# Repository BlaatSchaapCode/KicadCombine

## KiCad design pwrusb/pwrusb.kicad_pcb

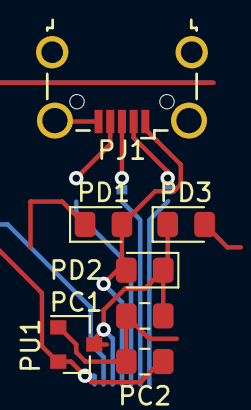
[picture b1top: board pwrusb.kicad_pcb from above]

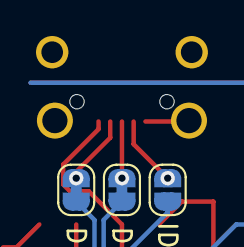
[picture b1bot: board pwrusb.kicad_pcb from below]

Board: 2 copper layers, 10 parts (3 on the bottom side), 7 nets.

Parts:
PC1, PC2: 1uF; C_0805_2012Metric_Pad1.15x1.40mm_HandSolder
PD1, PD2, PD3: D; D_0805_2012Metric_Pad1.15x1.40mm_HandSolder
PJ1: USB_B_Mini; USB_Micro-B_Wuerth_629105150521_CircularHoles
PSJ1: D+; SolderJumper-2_P1.3mm_Bridged_RoundedPad1.0x1.5mm
PSJ2: D-; SolderJumper-2_P1.3mm_Bridged_RoundedPad1.0x1.5mm
PSJ3: ID; SolderJumper-2_P1.3mm_Open_RoundedPad1.0x1.5mm
PU1: MCP1700-3302E_SOT23; SOT-23

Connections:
GND: PC1.2, PC2.2, PJ1.5, PJ1.6, PU1.1
unnamed: PJ1.2, PSJ2.1
unnamed: PJ1.3, PSJ1.1
unnamed: PJ1.4, PSJ3.1
VBUS: PD1.2, PD2.2, PJ1.1
VDD: PC2.1, PU1.2
VREG_IN: PC1.1, PD2.1, PD3.1, PU1.3

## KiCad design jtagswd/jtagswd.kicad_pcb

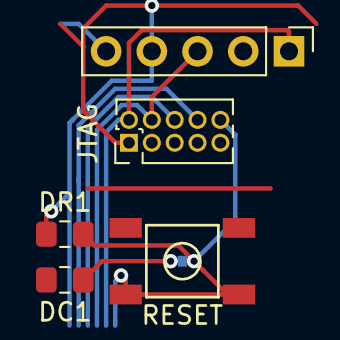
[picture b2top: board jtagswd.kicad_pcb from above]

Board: 2 copper layers, 6 parts (1 on the bottom side), 6 nets.

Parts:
DC1: 100nF; C_0805_2012Metric_Pad1.15x1.40mm_HandSolder
DJ1: JTAG; PinHeader_2x05_P1.27mm_Vertical
DJ2: Conn_01x05; PinHeader_1x05_P2.54mm_Vertical
DJP1: SolderJumper_2_Bridged; SolderJumper-2_P1.3mm_Bridged_RoundedPad1.0x1.5mm
DR1: 10K; R_0805_2012Metric_Pad1.15x1.40mm_HandSolder
DSW1: RESET; TS-1187

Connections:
GND: DC1.1, DJ1.3, DJ1.7, DJ1.9, DJ2.2, DSW1.2
unnamed: DC1.2, DJP1.2
TCK: DJ1.4, DJ2.3
TMS: DJ1.2, DJ2.1
VDD: DJ1.1, DJ2.4, DR1.1
~SRST: DJ1.10, DJP1.1, DR1.2, DSW1.1

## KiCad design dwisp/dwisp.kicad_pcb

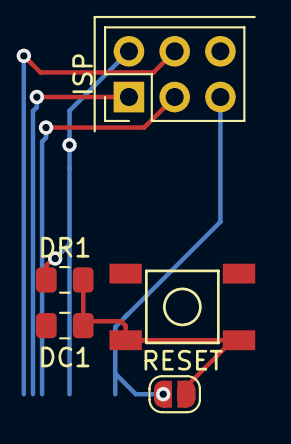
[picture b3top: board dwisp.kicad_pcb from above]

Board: 2 copper layers, 5 parts (0 on the bottom side), 4 nets.

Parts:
DC1: 100nF; C_0805_2012Metric_Pad1.15x1.40mm_HandSolder
DJ2: ISP; PinHeader_2x03_P2.54mm_Vertical
DJP1: SolderJumper_2_Open; SolderJumper-2_P1.3mm_Open_RoundedPad1.0x1.5mm
DR1: 10K; R_0805_2012Metric_Pad1.15x1.40mm_HandSolder
DSW1: RESET; TS-1187

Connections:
GND: DC1.1, DJ2.6, DSW1.2
unnamed: DC1.2, DJP1.2, DR1.2, DSW1.1
VDD: DJ2.2, DR1.1
~RESET: DJ2.5, DJP1.1

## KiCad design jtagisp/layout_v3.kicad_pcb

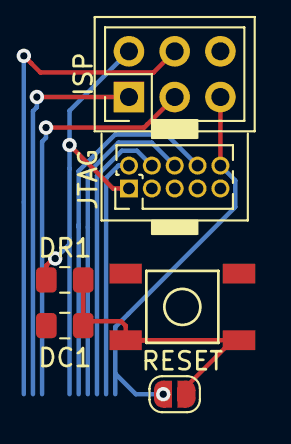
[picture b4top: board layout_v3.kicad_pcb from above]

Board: 2 copper layers, 6 parts (0 on the bottom side), 4 nets.

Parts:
DC1: 100nF; C_0805_2012Metric_Pad1.15x1.40mm_HandSolder
DJ1: JTAG; PinHeader_2x05_P1.27mm_Vertical
DJ2: ISP; PinHeader_2x03_P2.54mm_Vertical
DJP1: SolderJumper_2_Open; SolderJumper-2_P1.3mm_Open_RoundedPad1.0x1.5mm
DR1: 10K; R_0805_2012Metric_Pad1.15x1.40mm_HandSolder
DSW1: RESET; TS-1187

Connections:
GND: DC1.1, DJ1.3, DJ1.7, DJ1.9, DJ2.6, DSW1.2
unnamed: DC1.2, DJP1.2, DR1.2, DSW1.1
VDD: DJ1.1, DJ2.2, DR1.1
~RESET: DJ1.10, DJ2.5, DJP1.1

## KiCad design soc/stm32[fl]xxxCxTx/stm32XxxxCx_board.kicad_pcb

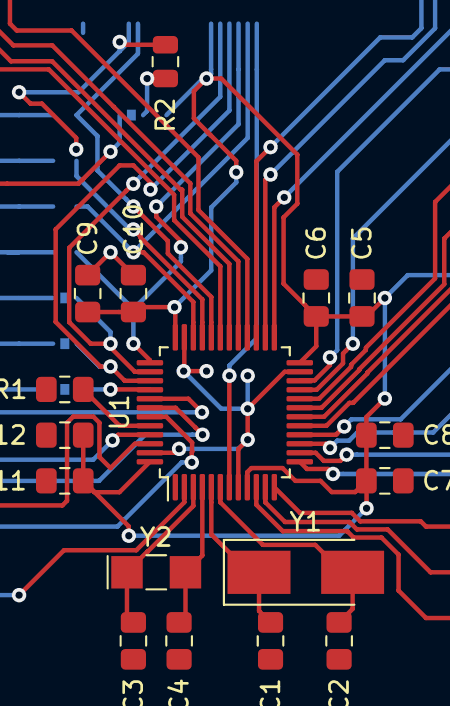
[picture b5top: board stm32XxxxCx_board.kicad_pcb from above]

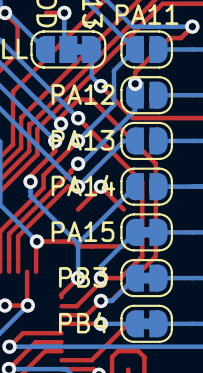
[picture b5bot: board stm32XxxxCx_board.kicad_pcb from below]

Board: 2 copper layers, 25 parts (8 on the bottom side), 16 nets.

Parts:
C1, C2, C3, C4: C; C_0805_2012Metric_Pad1.15x1.40mm_HandSolder
C5, C7, C9, C11: 1u; C_0805_2012Metric_Pad1.15x1.40mm_HandSolder
C6, C8, C10, C12: 100n; C_0805_2012Metric_Pad1.15x1.40mm_HandSolder
JP1: USBPULL; SolderJumper-3_P1.3mm_Bridged12_RoundedPad1.0x1.5mm
JP2: PA11; SolderJumper-2_P1.3mm_Open_RoundedPad1.0x1.5mm
JP3: PA12; SolderJumper-2_P1.3mm_Open_RoundedPad1.0x1.5mm
JP4: PA13; SolderJumper-2_P1.3mm_Open_RoundedPad1.0x1.5mm
JP5: PA14; SolderJumper-2_P1.3mm_Open_RoundedPad1.0x1.5mm
JP6: PA15; SolderJumper-2_P1.3mm_Bridged_RoundedPad1.0x1.5mm
JP7: PB3; SolderJumper-2_P1.3mm_Bridged_RoundedPad1.0x1.5mm
JP8: PB4; SolderJumper-2_P1.3mm_Bridged_RoundedPad1.0x1.5mm
R1: 10K; R_0805_2012Metric_Pad1.15x1.40mm_HandSolder
R2: 1K5; R_0805_2012Metric
U1: STM32F103CBTx; LQFP-48_7x7mm_P0.5mm
Y1: 8MHz, 20pF; Crystal_SMD_5032-2Pin_5.0x3.2mm_HandSoldering
Y2: 32KHz, 4pF; Crystal_SMD_EuroQuartz_EQ161-2Pin_3.2x1.5mm_HandSoldering

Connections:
BOOT0: R1.2, U1.44
GND: C1.2, C2.2, C3.2, C4.2, C5.2, C6.2, C7.2, C8.2, C9.2, C10.2, C11.2, C12.2, R1.1, U1.8, U1.23, U1.35, U1.47
unnamed: JP1.2, R2.1
PA13: JP4.2, U1.34
PA14: JP5.2, U1.37
PA15: JP6.2, U1.38
PB3: JP7.2, U1.39
PB4: JP8.2, U1.40
PC13: JP1.1, U1.2
PC14: C3.1, U1.3, Y2.1
PC15: C4.1, U1.4, Y2.2
PF0: C1.1, U1.5, Y1.1
PF1: C2.1, U1.6, Y1.2
USB_D+: JP3.2, R2.2, U1.33
USB_D-: JP2.2, U1.32
VDD: C5.1, C6.1, C7.1, C8.1, C9.1, C10.1, C11.1, C12.1, JP1.3, U1.9, U1.24, U1.36, U1.48

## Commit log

2019-05-08 Minor changes after first combine
2019-05-08 Gitignore file to ignore backup/cache files
2019-05-09 added JTAG + ISP layout for bigger AVR chips (eg. ATmega1284P) (Not tested with other layouts yet)
2019-05-09 Added DWISP, for smaller AVR (eg. ATMEGA328P), derived from JTAGISP with Cortex header removed
2019-05-09 WIP STM32{F,L}xxxCxTx layout
2019-05-11 Defining areas and connections per 'module'
2019-05-11 Changes after combining
2019-05-11 Initial Combinator Script
2019-05-11 File Renames for Scripting
2019-05-11 Adjust combiner to accept subdirectories + rename stm32 files for combiner
